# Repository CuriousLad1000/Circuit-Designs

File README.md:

# Circuit Designs

## About circuits repository

This Repository will have a collection of various circuit designs built
by me that were either a part of a bigger project or were a part of some
DIY hobby project. Each of the circuit design is listed under its own
sub-section with its own details listed under it.

## Sample pics

**Contactless temperature measure**

<br/>

<br/>

<br/>
<br/>

**Infrared sensor circuit board**

<br/>

<br/>
<br/>

**Temperature cube**

<br/>

<br/>
<br/>

**Tesseract**

<br/>

<br/>

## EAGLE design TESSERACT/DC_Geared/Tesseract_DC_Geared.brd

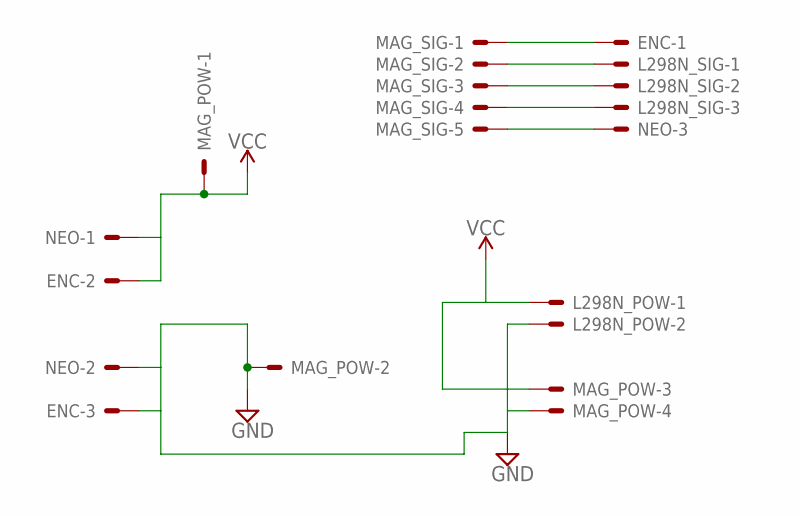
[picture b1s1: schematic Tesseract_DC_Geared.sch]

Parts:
ENC: JST-XH-03-PIN-LONG-PAD; JST-XH-03-PACKAGE-LONG-PAD
L298N_POW: JST-XH-02-PIN-LONG-PAD; JST-XH-02-PACKAGE-LONG-PAD
L298N_SIG: JST-XH-03-PIN-LONG-PAD; JST-XH-03-PACKAGE-LONG-PAD
MAG_POW: JST-XH-04-PIN-LONG-PAD; JST-XH-04-PACKAGE-LONG-PAD
MAG_SIG: JST-XH-05-PIN-LONG-PAD; JST-XH-05-PACKAGE-LONG-PAD
NEO: JST-XH-03-PIN-LONG-PAD; JST-XH-03-PACKAGE-LONG-PAD

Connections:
5V_GND: ENC.3, L298N_POW.2, MAG_POW.2, MAG_POW.4, NEO.2
5V_VCC: ENC.2, MAG_POW.1, NEO.1
12V_VCC: L298N_POW.1, MAG_POW.3
PIN3: ENC.1, MAG_SIG.1
PIN4: L298N_SIG.1, MAG_SIG.2
PIN5: L298N_SIG.2, MAG_SIG.3
PIN6: L298N_SIG.3, MAG_SIG.4
PIN7: MAG_SIG.5, NEO.3

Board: 2 copper layers, 6 parts (0 on the bottom side), 8 nets, no tracks yet.

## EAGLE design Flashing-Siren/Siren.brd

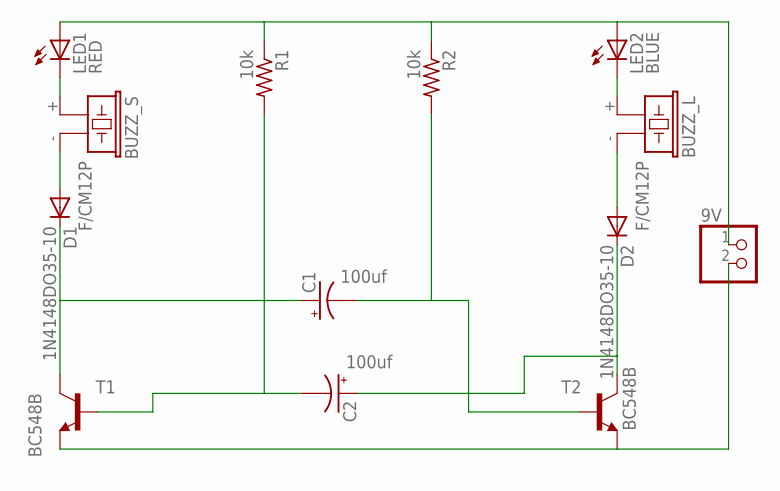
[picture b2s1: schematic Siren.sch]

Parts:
9V: PINHD-1X2; 1X02
BUZZ_L: F/CM12P
BUZZ_S: F/CM12P
C1, C2: 100uf; E2,5-5
D1, D2: 1N4148DO35-10; DO35-10
LED1: RED; LED5MM
LED2: BLUE; LED5MM
R1, R2: 10k; 0204/7
T1, T2: BC548B; TO92-CBE

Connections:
unnamed: BUZZ_S.+ (1), LED1.K (C)
unnamed: BUZZ_S.- (2), D1.A
unnamed: C1.+, D1.C, T1.C
unnamed: 9V.2, T1.E, T2.E
unnamed: BUZZ_L.+ (1), LED2.K (C)
unnamed: BUZZ_L.- (2), D2.A
unnamed: C2.+, D2.C, T2.C
unnamed: C2.-, R1.2, T1.B
unnamed: C1.-, R2.2, T2.B
unnamed: 9V.1, LED1.A, LED2.A, R1.1, R2.1

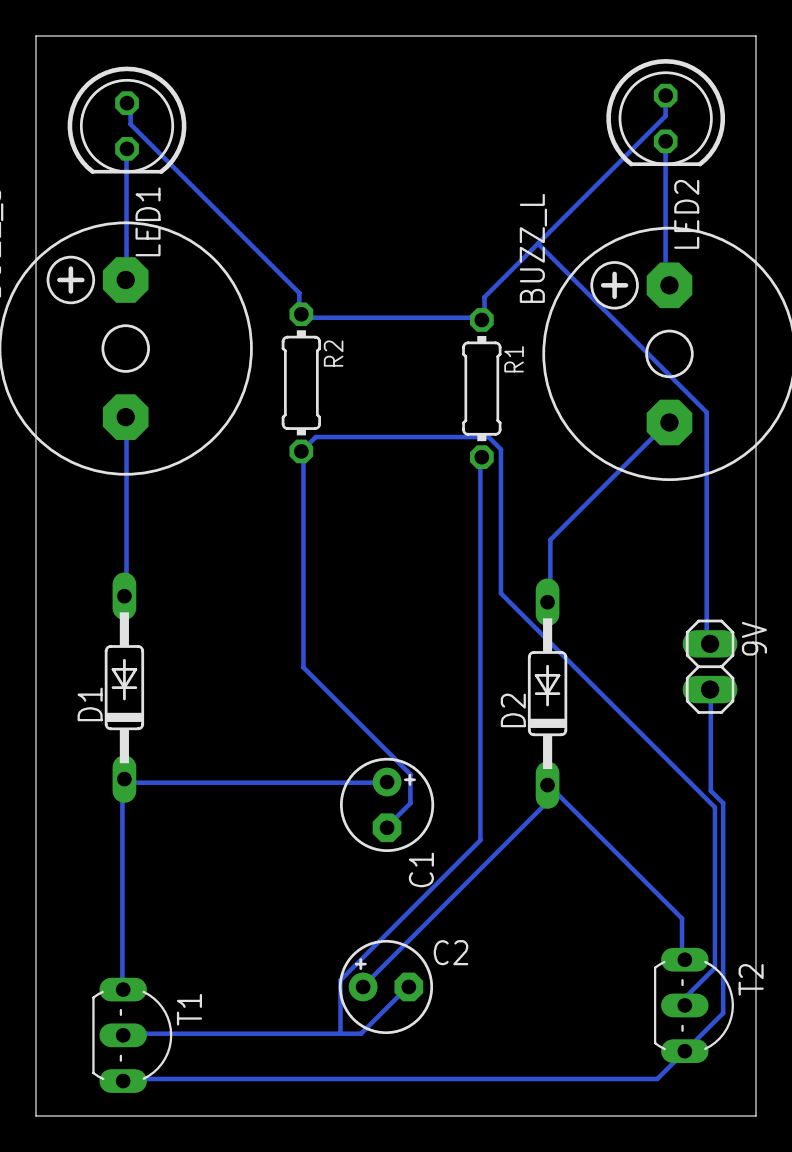
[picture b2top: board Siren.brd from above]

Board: 2 copper layers, 40.0 x 60.0 mm, 13 parts (0 on the bottom side), 10 nets.

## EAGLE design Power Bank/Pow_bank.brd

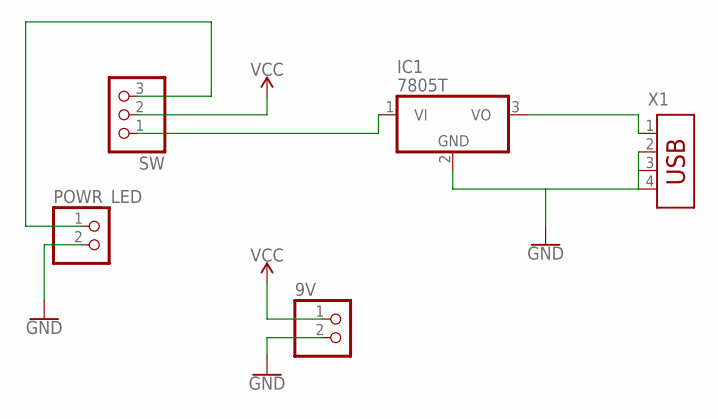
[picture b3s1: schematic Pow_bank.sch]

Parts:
9V: PINHD-1X2; 1X02
IC1: 7805T; TO220H
POWR_LED: PINHD-1X2; 1X02
SW: PINHD-1X3; 1X03
X1: USB-787616; USB

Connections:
GND: 9V.2, IC1.2 (GND), POWR_LED.2, X1.2, X1.3, X1.4
unnamed: IC1.1 (VI), SW.1
unnamed: IC1.3 (VO), X1.1
unnamed: POWR_LED.1, SW.3
VCC: 9V.1, SW.2

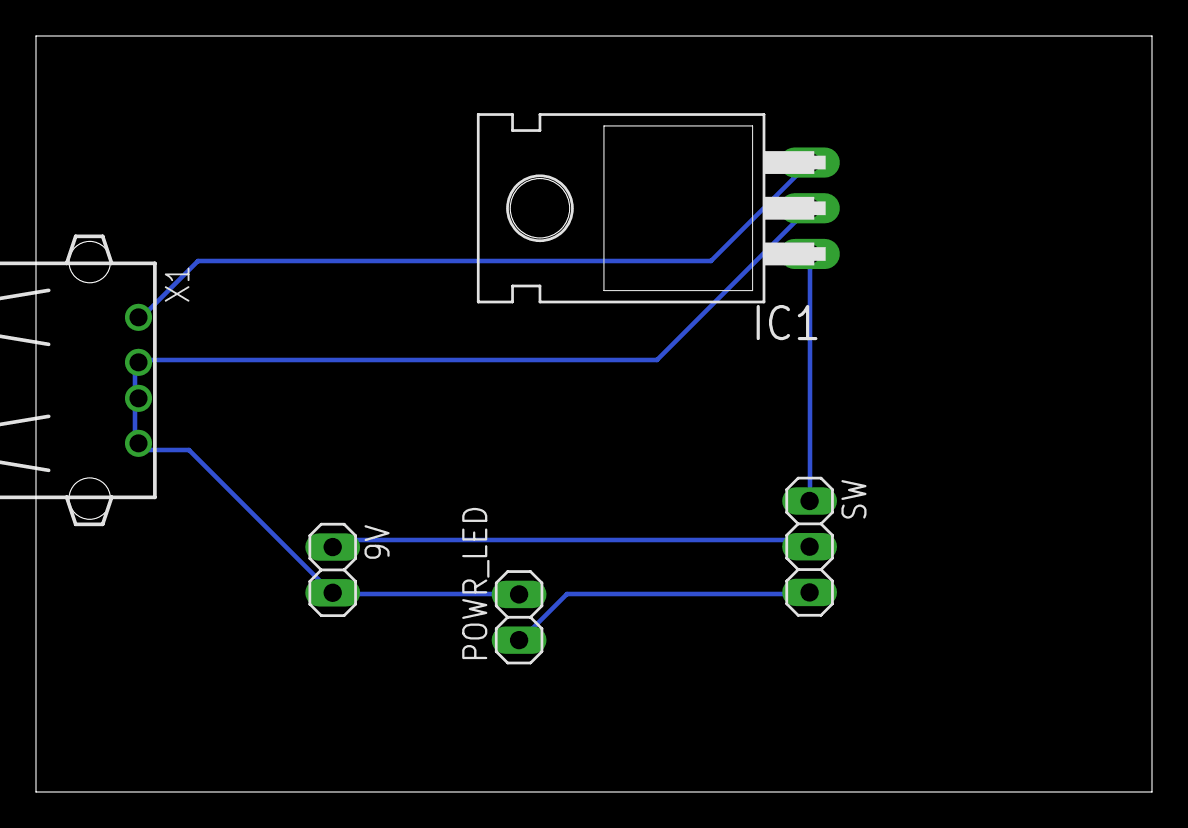
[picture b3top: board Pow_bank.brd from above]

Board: 2 copper layers, 62.0 x 42.0 mm, 5 parts (0 on the bottom side), 5 nets.

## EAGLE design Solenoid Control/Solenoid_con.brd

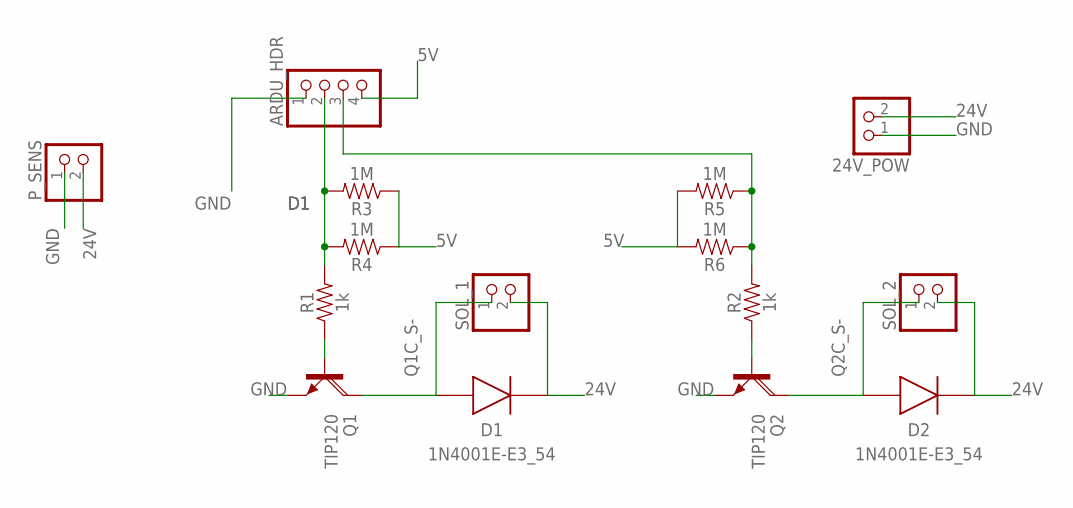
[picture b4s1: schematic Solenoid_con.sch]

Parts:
24V_POW: PINHD-1X2; 1X02
ARDU_HDR: PINHD-1X4; 1X04
D1, D2: 1N4001E-E3_54; DIOAD1405W86L465D235
P_SENS: PINHD-1X2; 1X02
Q1, Q2: TIP120; TO220AH
R1, R2: 1k; AXIAL-0.3
R3, R4, R5, R6: 1M; AXIAL-0.3
SOL_1, SOL_2: PINHD-1X2; 1X02

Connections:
5V: ARDU_HDR.4, R3.P$1 (1), R4.P$1 (1), R5.P$2 (2), R6.P$2 (2)
24V: 24V_POW.2, D1.2 (K), D2.2 (K), P_SENS.2, SOL_1.2, SOL_2.2
D1: ARDU_HDR.2, R1.P$2 (2), R3.P$2 (2), R4.P$2 (2)
D2: ARDU_HDR.3, R2.P$2 (2), R5.P$1 (1), R6.P$1 (1)
GND: 24V_POW.1, ARDU_HDR.1, P_SENS.1, Q1.E, Q2.E
unnamed: Q1.B, R1.P$1 (1)
unnamed: Q2.B, R2.P$1 (1)
Q1C_S-: D1.1 (A), Q1.C, SOL_1.1
Q2C_S-: D2.1 (A), Q2.C, SOL_2.1

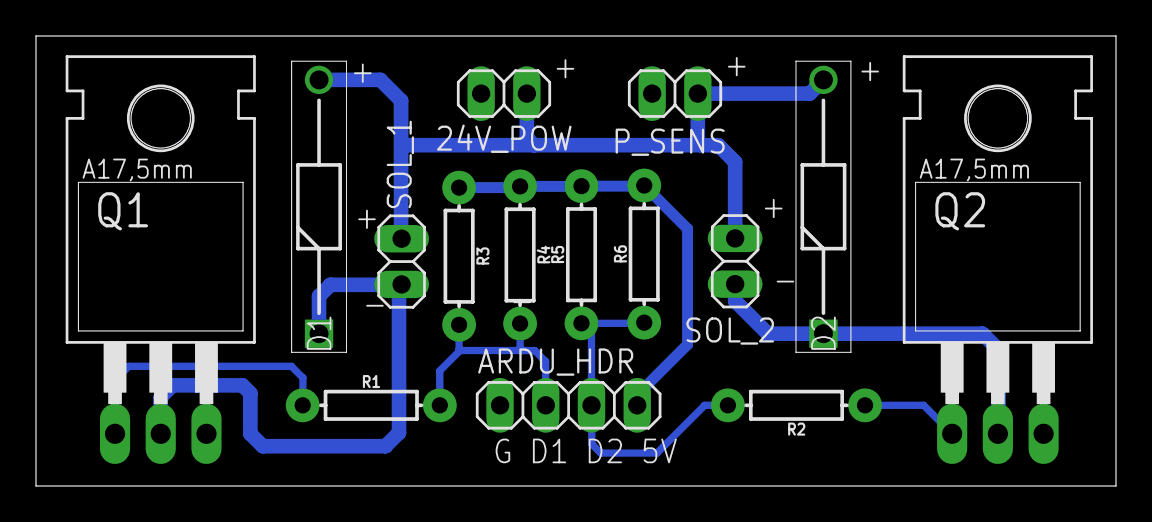
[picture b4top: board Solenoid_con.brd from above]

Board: 2 copper layers, 60.0 x 25.0 mm, 15 parts (0 on the bottom side), 9 nets.

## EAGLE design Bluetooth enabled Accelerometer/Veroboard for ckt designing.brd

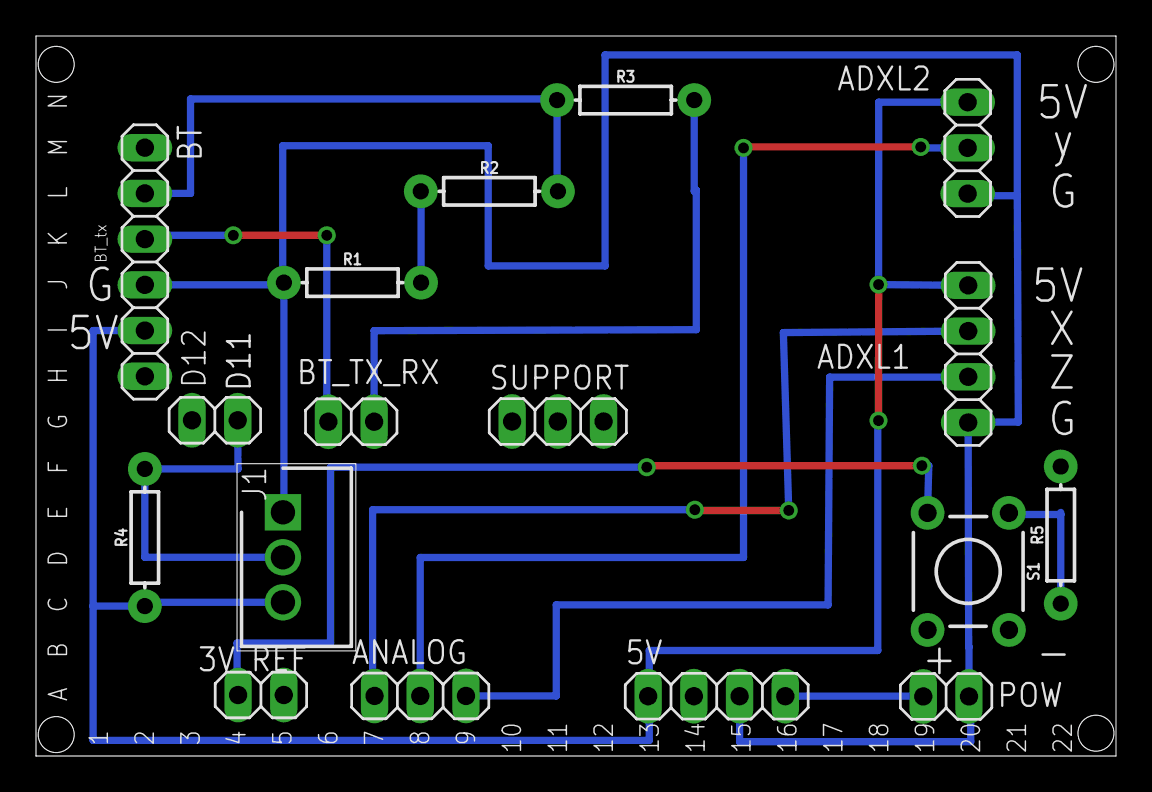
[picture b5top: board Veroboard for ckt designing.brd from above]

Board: 2 copper layers, 60.0 x 40.0 mm, 39 parts (0 on the bottom side), 13 nets.

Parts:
3V_REF: 1X02
5V: 1X04
ADXL1: 1X04
ADXL2: 1X03
ANALOG: 1X03
BT: 1X06
BT_TX_RX: 1X02
D11: 1X02
J1: S3B-XH-A(LF)(SN); SHDR3W80P0X250_1X3_990X610X700
POW: 1X02
R1, R2, R3, R5: 1k; AXIAL-0.3
R4: 4.7k; AXIAL-0.3
S1: TACTILE_SWITCH_PTH_6.0MM
SUPPORT: 1X03
U$1, U$2, U$3, U$4, U$5, U$6, U$7, U$8, U$9, U$10, U$11, U$12, U$13, U$14, U$15, U$16, U$17, U$18, U$19, U$20, U$21, U$22: 1X14

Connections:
3V: 3V_REF.1, S1.3
5V: 5V.1, ADXL1.4, ADXL2.1, BT.5, J1.3, R4.P$1
BT_TX: BT.3, BT_TX_RX.2
G: 5V.3, ADXL1.1, ADXL2.3, BT.4, J1.1, POW.2, R1.P$1
unnamed: R1.P$2, R2.P$1
unnamed: BT.2, R2.P$2, R3.P$1
unnamed: R5.P$1, S1.1
RX: BT_TX_RX.1, R3.P$2
TS: D11.1, J1.2, R4.P$2
VIN: 5V.4, POW.1
X: ADXL1.3, ANALOG.1
Y: ADXL2.2, ANALOG.2
Z: ADXL1.2, ANALOG.3

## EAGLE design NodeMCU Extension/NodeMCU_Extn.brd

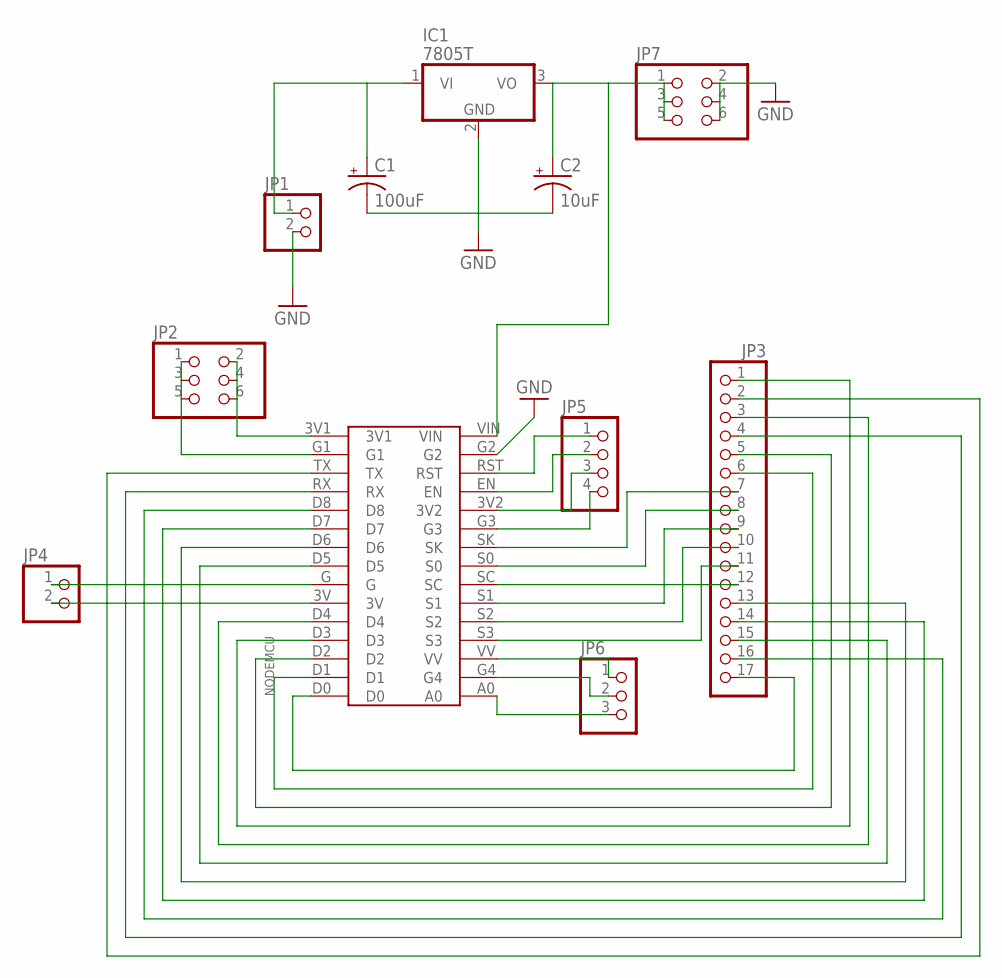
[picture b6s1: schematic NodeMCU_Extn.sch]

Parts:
C1: 100uF; CPOL-RADIAL-2.5MM-5MM
C2: 10uF; CPOL-RADIAL-2.5MM-5MM
IC1: 7805T; TO220H
JP1, JP4: PINHD-1X2; 1X02
JP2, JP7: PINHD-2X3; 2X03
JP3: PINHD-1X17; 1X17
JP5: PINHD-1X4; 1X04
JP6: PINHD-1X3; 1X03
NODEMCU: LOLIN

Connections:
3V3: JP2.2, JP2.4, JP2.6, NODEMCU.3V1
5V: C2.1 (+), IC1.3 (VO), JP7.1, JP7.3, JP7.5, NODEMCU.VIN
9V: C1.1 (+), IC1.1 (VI), JP1.1
A0: JP6.3, NODEMCU.A0
EN: JP5.2, NODEMCU.EN
GND: C1.2 (-), C2.2 (-), IC1.2 (GND), JP1.2, JP7.2, JP7.4, JP7.6, NODEMCU.G2
G_MCU: JP2.1, JP2.3, JP2.5, NODEMCU.G1
IO0: JP3.1, NODEMCU.D3
IO1: JP3.2, NODEMCU.TX
IO2: JP3.3, NODEMCU.D4
IO3: JP3.4, NODEMCU.RX
IO4: JP3.5, NODEMCU.D2
IO5: JP3.6, NODEMCU.D1
IO6: JP3.7, NODEMCU.SK
IO7: JP3.8, NODEMCU.S0
IO8: JP3.9, NODEMCU.S1
IO9: JP3.10, NODEMCU.S2
IO10: JP3.11, NODEMCU.S3
IO11: JP3.12, NODEMCU.SC
IO12: JP3.13, NODEMCU.D6
IO13: JP3.14, NODEMCU.D7
IO14: JP3.15, NODEMCU.D5
IO15: JP3.16, NODEMCU.D8
IO16: JP3.17, NODEMCU.D0
unnamed: JP4.1, NODEMCU.G
unnamed: JP4.2, NODEMCU.3V
unnamed: JP5.4, NODEMCU.G3
unnamed: JP6.1, NODEMCU.VV
unnamed: JP6.2, NODEMCU.G4
unnamed: JP5.3, NODEMCU.3V2
RST: JP5.1, NODEMCU.RST

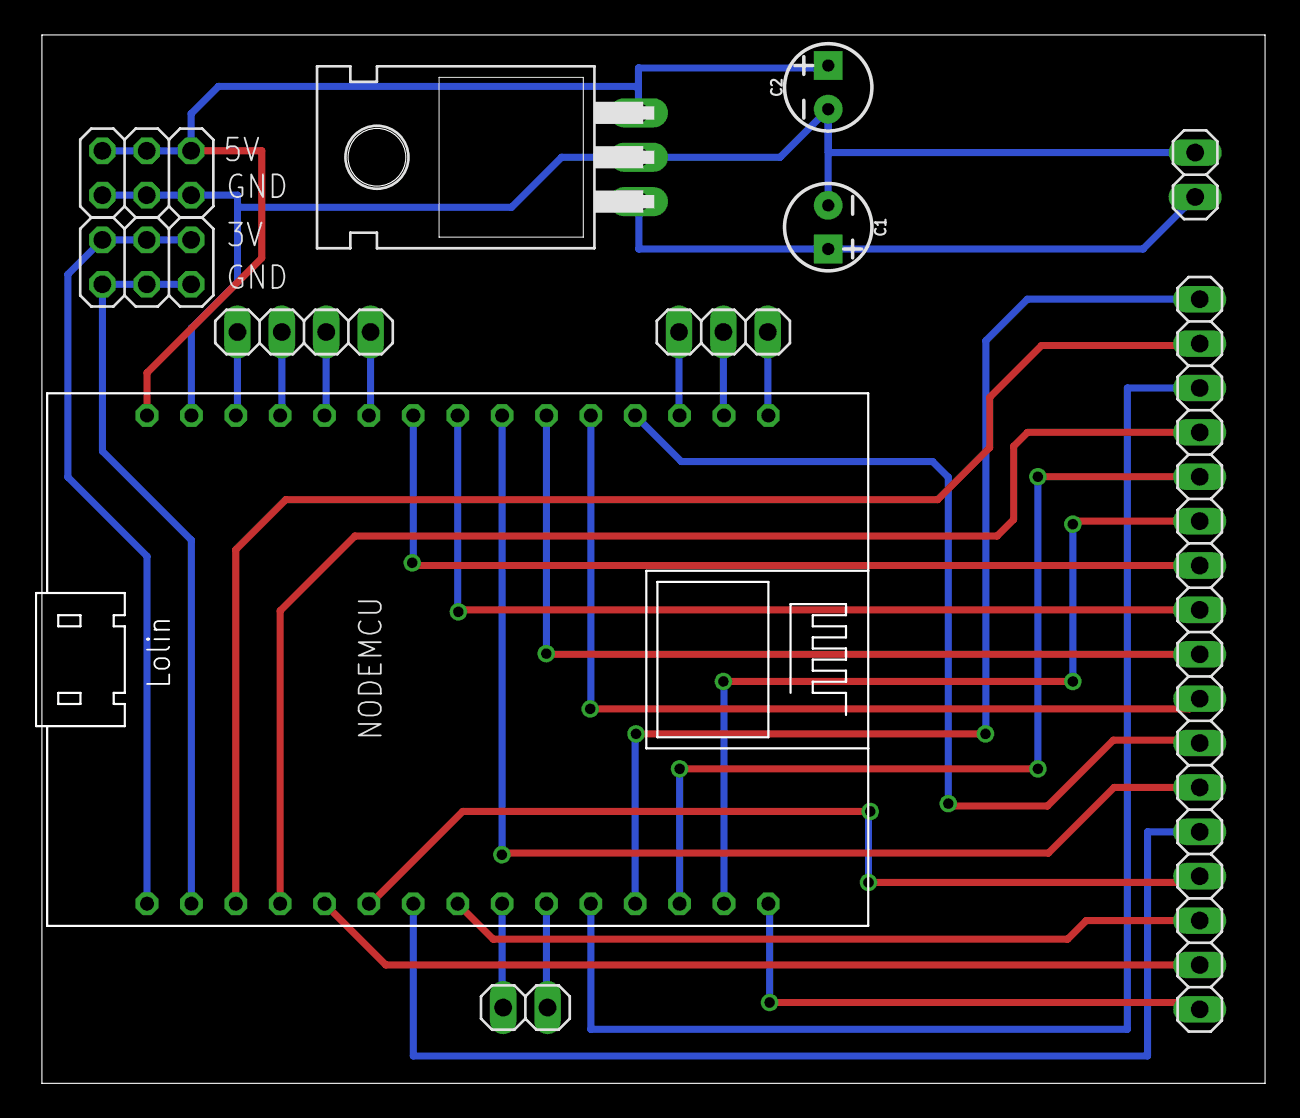
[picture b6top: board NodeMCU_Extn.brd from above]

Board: 2 copper layers, 70.3 x 59.9 mm, 11 parts (0 on the bottom side), 31 nets.

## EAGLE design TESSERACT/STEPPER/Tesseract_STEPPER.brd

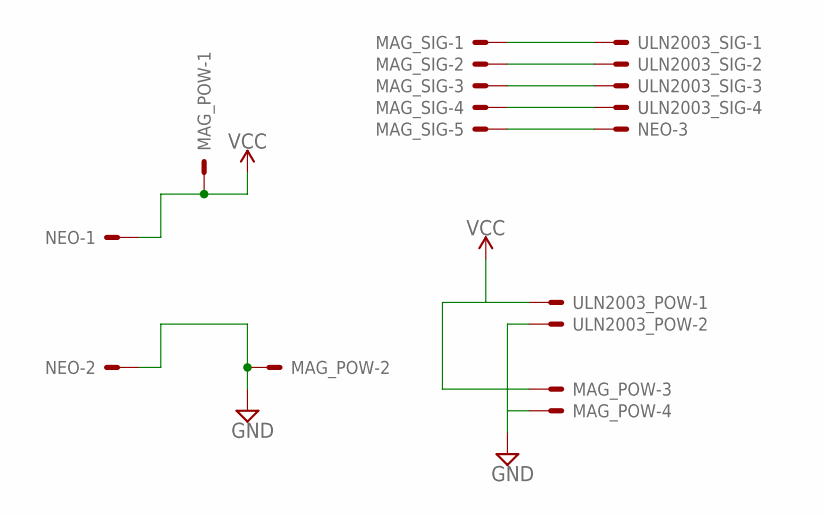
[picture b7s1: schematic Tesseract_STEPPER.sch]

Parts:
MAG_POW: JST-XH-04-PIN-LONG-PAD; JST-XH-04-PACKAGE-LONG-PAD
MAG_SIG: JST-XH-05-PIN-LONG-PAD; JST-XH-05-PACKAGE-LONG-PAD
NEO: JST-XH-03-PIN-LONG-PAD; JST-XH-03-PACKAGE-LONG-PAD
ULN2003_POW: JST-XH-02-PIN-LONG-PAD; JST-XH-02-PACKAGE-LONG-PAD
ULN2003_SIG: JST-XH-04-PIN-LONG-PAD; JST-XH-04-PACKAGE-LONG-PAD

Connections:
5V_GND: MAG_POW.2, NEO.2
5V_VCC: MAG_POW.1, NEO.1
12V_GND: MAG_POW.4, ULN2003_POW.2
12V_VCC: MAG_POW.3, ULN2003_POW.1
PIN3: MAG_SIG.1, ULN2003_SIG.1
PIN4: MAG_SIG.2, ULN2003_SIG.2
PIN5: MAG_SIG.3, ULN2003_SIG.3
PIN6: MAG_SIG.4, ULN2003_SIG.4
PIN7: MAG_SIG.5, NEO.3

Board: 2 copper layers, 5 parts (0 on the bottom side), 9 nets, no tracks yet.

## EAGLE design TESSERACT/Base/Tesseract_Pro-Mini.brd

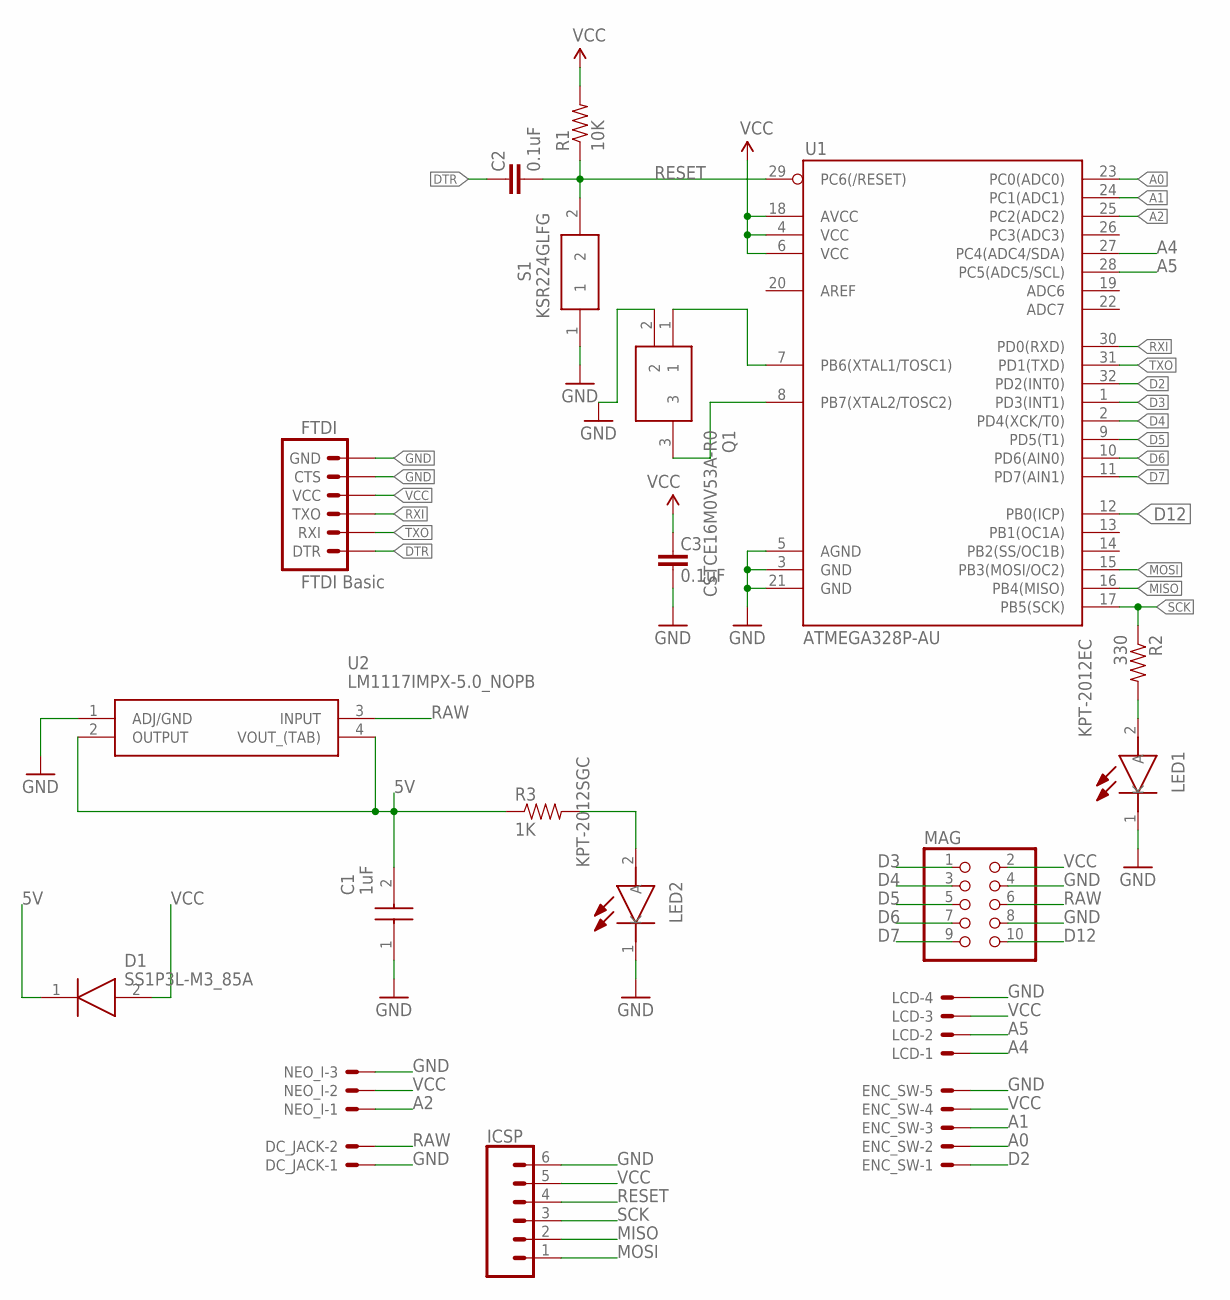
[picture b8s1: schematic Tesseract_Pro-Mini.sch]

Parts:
C1: 1uF; CAPC1608X90N
C2, C3: 0.1uF; 0603-CAP
D1: SS1P3L-M3_85A; SMP
DC_JACK: JST-XH-02-PIN-LONG-PAD; JST-XH-02-PACKAGE-LONG-PAD
ENC_SW: JST-XH-05-PIN-LONG-PAD; JST-XH-05-PACKAGE-LONG-PAD
FTDI: FTDI Basic; 1X06
ICSP: CONN_06NO_SILK_NO_POP; 1X06_NO_SILK
LCD: JST-XH-04-PIN-LONG-PAD; JST-XH-04-PACKAGE-LONG-PAD
LED1: KPT-2012EC; LEDC2012X75N
LED2: KPT-2012SGC; LEDM2012X120N
MAG: PINHD-2X5; 2X05
NEO_I: JST-XH-03-PIN-LONG-PAD; JST-XH-03-PACKAGE-LONG-PAD
Q1: CSTCE16M0V53A-R0; CSTCE-V_1
R1: 10K; 0603-RES
R2: 330; 0603-RES
R3: 1K; 0603-RES
S1: KSR224GLFG; KSR211GLFS
U1: ATMEGA328P-AU; TQFP32-08; PART_NUMBER ATMEGA328P-AU
U2: LM1117IMPX-5.0_NOPB; SOT230P700X180-4N

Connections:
5V: C1.2, D1.1 (A), R3.1, U2.2 (OUTPUT), U2.4 (VOUT_(TAB))
A0: ENC_SW.2, U1.23 (PC0(ADC0))
A1: ENC_SW.3, U1.24 (PC1(ADC1))
A2: NEO_I.1, U1.25 (PC2(ADC2))
A4: LCD.1, U1.27 (PC4(ADC4/SDA))
A5: LCD.2, U1.28 (PC5(ADC5/SCL))
D2: ENC_SW.1, U1.32 (PD2(INT0))
D3: MAG.1, U1.1 (PD3(INT1))
D4: MAG.3, U1.2 (PD4(XCK/T0))
D5: MAG.5, U1.9 (PD5(T1))
D6: MAG.7, U1.10 (PD6(AIN0))
D7: MAG.9, U1.11 (PD7(AIN1))
D12: MAG.10, U1.12 (PB0(ICP))
DTR: C2.2, FTDI.1 (DTR)
GND: C1.1, C3.1, DC_JACK.1, ENC_SW.5, FTDI.5 (CTS), FTDI.6 (GND), ICSP.6, LCD.4, LED1.1 (K), LED2.1 (K), MAG.4, MAG.8, NEO_I.3, Q1.2, S1.1, U1.3 (GND), U1.5 (AGND), U1.21 (GND), U2.1 (ADJ/GND)
MISO: ICSP.2, U1.16 (PB4(MISO))
MOSI: ICSP.1, U1.15 (PB3(MOSI/OC2))
unnamed: Q1.1, U1.7 (PB6(XTAL1/TOSC1))
unnamed: Q1.3, U1.8 (PB7(XTAL2/TOSC2))
unnamed: LED2.2 (A), R3.2
unnamed: LED1.2 (A), R2.2
RAW: DC_JACK.2, MAG.6, U2.3 (INPUT)
RESET: C2.1, ICSP.4, R1.1, S1.2, U1.29 (PC6(/RESET))
RXI: FTDI.3 (TXO), U1.30 (PD0(RXD))
SCK: ICSP.3, R2.1, U1.17 (PB5(SCK))
TXO: FTDI.2 (RXI), U1.31 (PD1(TXD))
VCC: C3.2, D1.2 (K), ENC_SW.4, FTDI.4 (VCC), ICSP.5, LCD.3, MAG.2, NEO_I.2, R1.2, U1.4 (VCC), U1.6 (VCC), U1.18 (AVCC)

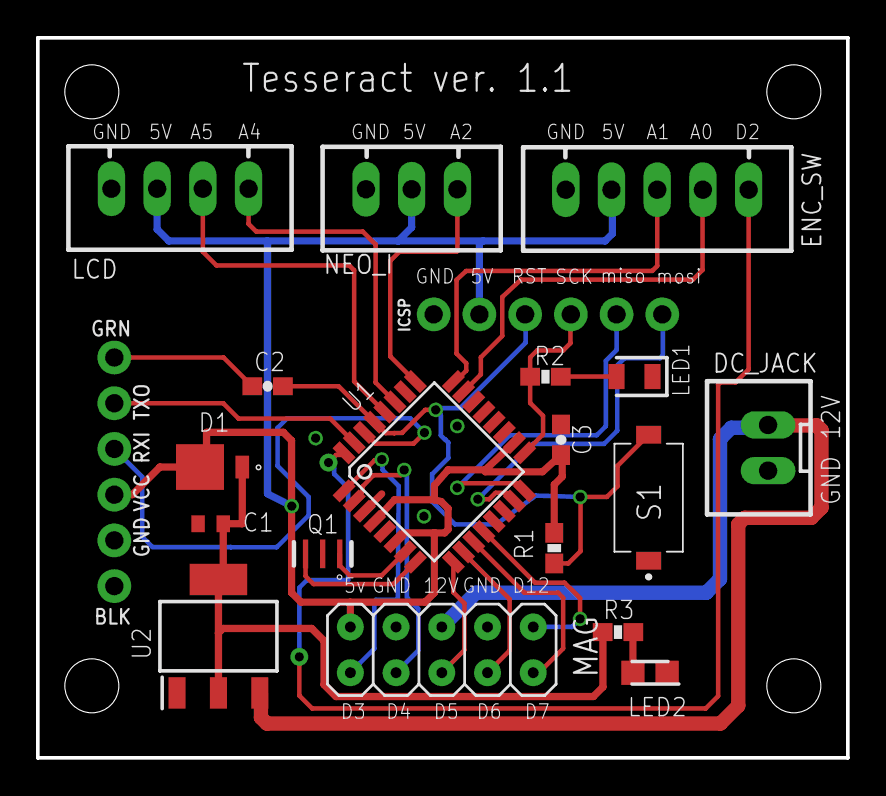
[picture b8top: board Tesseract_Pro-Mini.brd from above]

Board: 2 copper layers, 45.0 x 40.0 mm, 20 parts (1 on the bottom side), 27 nets.

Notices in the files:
parts and their libraries:
SparkFun-Resistors: Licensing: Creative Commons ShareAlike 4.0 International - https://creativecommons.org/licenses/by-sa/4.0
